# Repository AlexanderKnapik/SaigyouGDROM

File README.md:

SaigyouGDROM
========

SaigyouGDROM is a redesigned hardware implementation for Marcus Comstedt's
"iceGDROM". The aim of the project is to use the original software and gateware,
but with the hardware redesigned for a complete package.

This is currently a work in progress. Although the first revision prototypes have
been manufactured, there is still a lot to do in regards for testing and
recompiling the firmware and gateware for the new hardware.

For more information, please do visit the [original project](https://github.com/zeldin/iceGDROM).

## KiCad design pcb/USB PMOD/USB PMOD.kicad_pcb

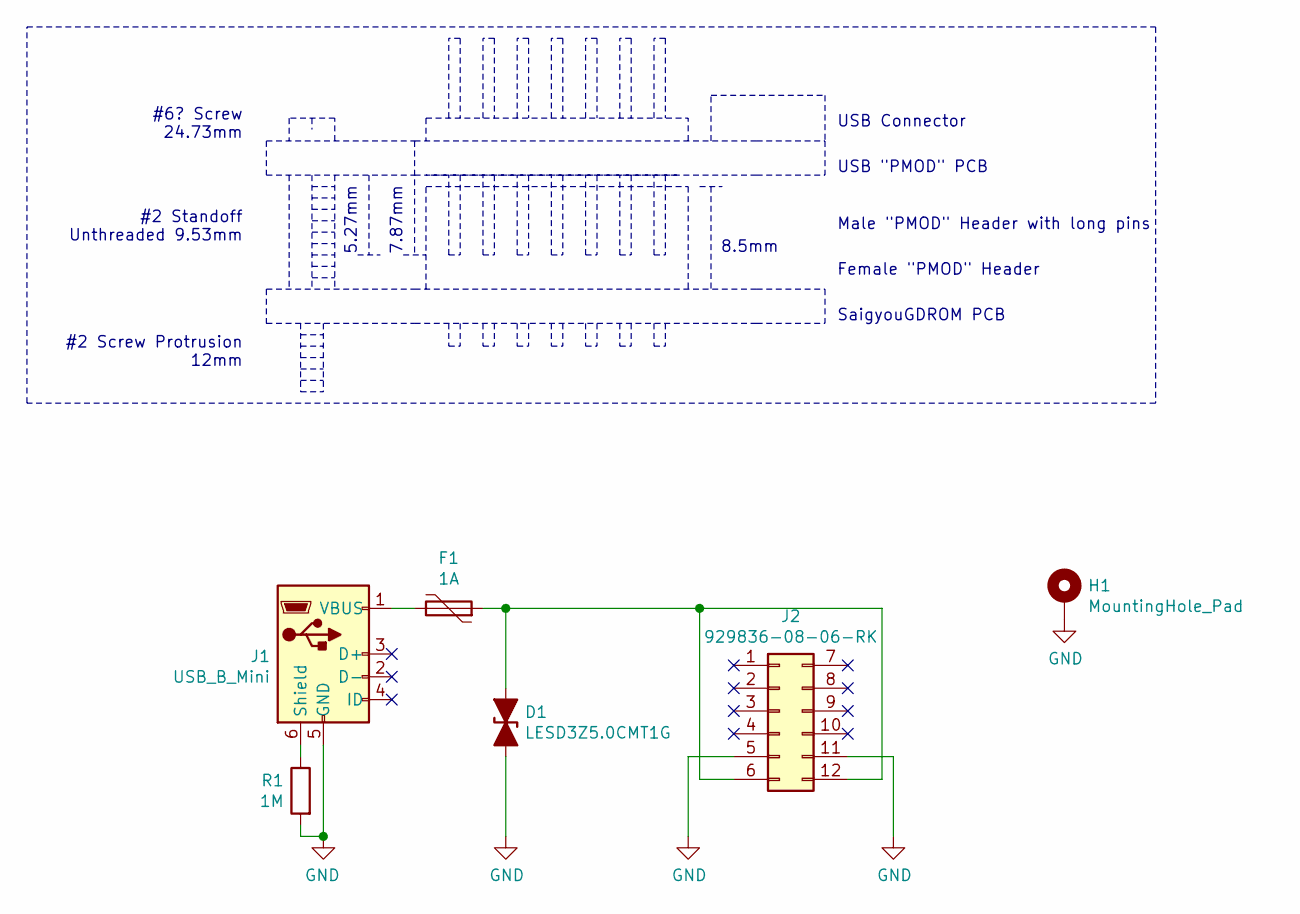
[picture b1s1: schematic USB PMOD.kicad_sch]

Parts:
D1: LESD3Z5.0CMT1G; D_SOD-323
F1: 1A; Fuse_1210_3225Metric_Castellated
H1: MountingHole_Pad; MountingHole_3.2mm_M3_Pad_Via
J1: USB_B_Mini; USB_Mini-B_Molex_657031020_Horizontal
J2: 929836-08-06-RK; PMOD_Host_2x06_P2.54mm_Vertical
R1: 1M; R_0603_1608Metric

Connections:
GND: D1.1 (A1), H1.1, J1.5 (GND), J2.5, J2.11, R1.2
unnamed: D1.2 (A2), F1.1, J2.6, J2.12
unnamed: F1.2, J1.1 (VBUS)
unnamed: J1.6 (Shield), R1.1

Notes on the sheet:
#6? Screw 24.73mm
#2 Standoff Unthreaded 9.53mm
#2 Screw Protrusion 12mm
5.27mm
7.87mm
8.5mm
USB Connector
USB "PMOD" PCB
Male "PMOD" Header with long pins
Female "PMOD" Header
SaigyouGDROM PCB

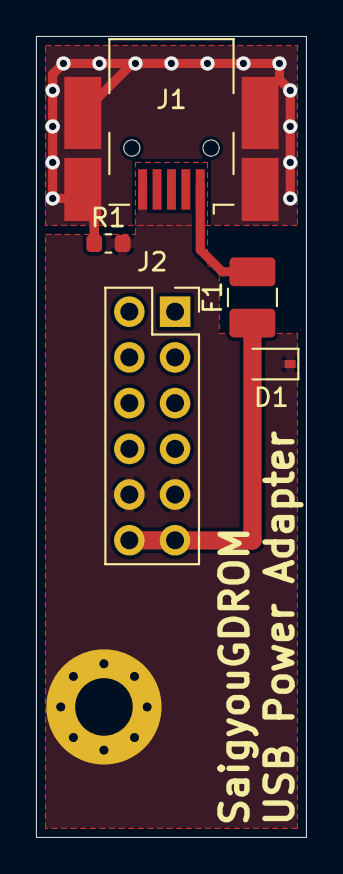
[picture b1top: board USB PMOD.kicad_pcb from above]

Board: 2 copper layers, 15.0 x 44.5 mm, 6 parts (0 on the bottom side), 4 nets.

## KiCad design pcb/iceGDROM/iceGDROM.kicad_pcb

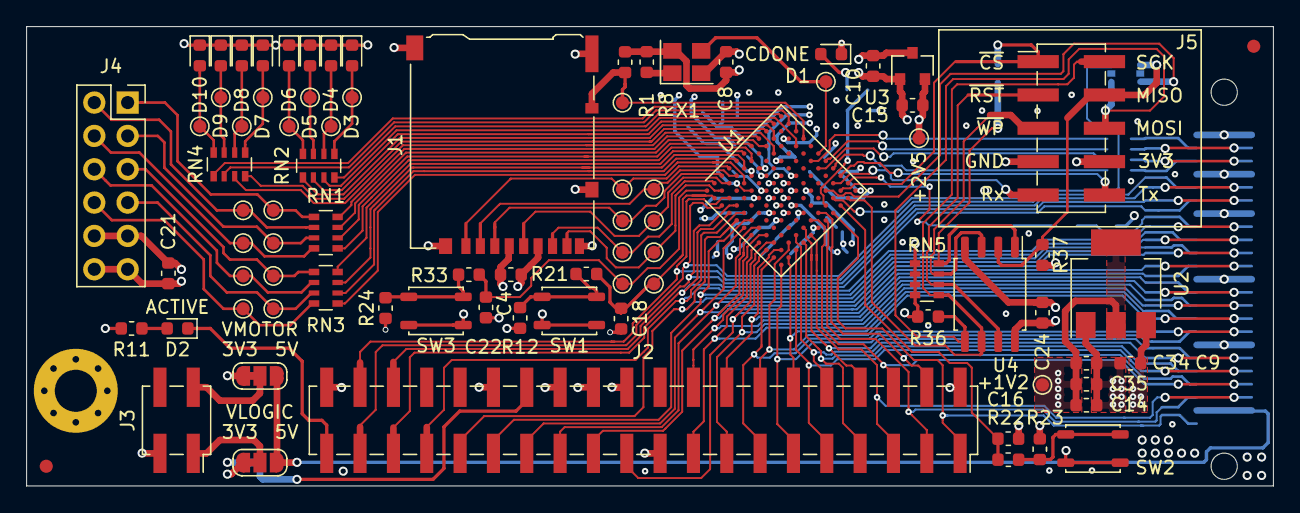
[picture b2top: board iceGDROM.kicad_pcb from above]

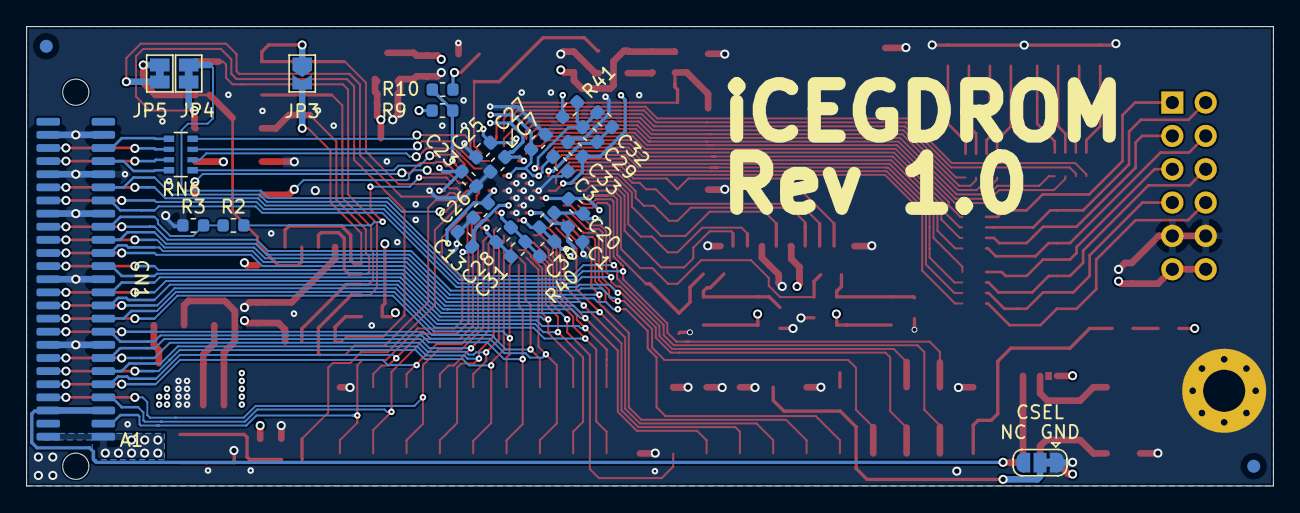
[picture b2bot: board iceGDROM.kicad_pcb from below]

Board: 4 copper layers, 95.0 x 35.0 mm, 114 parts (29 on the bottom side), 113 nets.

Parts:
+1V2, +2V5: TestPoint; TestPoint_Pad_D1.0mm
C1, C3, C4, C7, C8, C13, C20, C23, C24, C25, C26, C27, C28, C29, C30, C33: 100n; C_0603_1608Metric
C9, C14, C31, C32, C35: 10u; C_0603_1608Metric
C10, C15, C34: 1u0; C_0603_1608Metric
C16, C18, C22: 10n; C_0603_1608Metric
C21: NP; C_0603_1608Metric
CN1: Molex_52602_0579; Molex_052602_0579
D1, D2, D3, D4, D5, D6, D7, D8, D9, D10: LED; LED_0603_1608Metric
FID1, FID2, FID3, FID4: Fiducial; Fiducial_1mm_Mask2mm
H1: MountingHole_Pad; MountingHole_3.2mm_M3_Pad_Via
J1: Micro_SD_Card_Det_Hirose_DM3AT; microSD_HC_Hirose_DM3AT-SF-PEJM5
J2: Conn_02x20_Odd_Even; PinSocket_2x20_P2.54mm_Vertical_SMD
J3: Conn_02x02_Odd_Even; PinSocket_2x02_P2.54mm_Vertical_SMD
J4: PMOD; PMOD_Host_2x06_P2.54mm_Vertical
J5: Conn_02x05_Odd_Even; PinHeader_2x05_P2.54mm_Vertical_SMD
JP1: Jumper_NC_Dual; SolderJumper-3_P1.3mm_Bridged12_RoundedPad1.0x1.5mm
JP2, JP6: Jumper_3_Bridged12; SolderJumper-3_P1.3mm_Bridged12_RoundedPad1.0x1.5mm_NumberL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
JP3: SolderJumper_2_Bridged; SolderJumper-2_P1.3mm_Open_TrianglePad1.0x1.5mm
JP4, JP5: Jumper_NC_Small; SolderJumper-2_P1.3mm_Bridged_Pad1.0x1.5mm
R1, R3, R8, R12, R21, R22, R23, R24, R33: 10K; R_0603_1608Metric
R2, R40, R41: 100R; R_0603_1608Metric
R9: R; R_0603_1608Metric
R10, R11: 1K; R_0603_1608Metric
R36, R37: NP; R_0603_1608Metric
RN1, RN3, RN5: 10K; R_Array_Convex_4x0603
RN2, RN4: R_Pack04; R_Array_Convex_4x0603
RN6: 100R; R_Array_Convex_4x0603
SW1, SW2, SW3: SW_Push; SW_Push_SPST_NO_Alps_SKRP
TP2, TP3, TP4, TP5, TP6, TP7, TP8, TP9, TP10, TP11, TP12, TP13, TP14, TP15, TP16, TP17, TP18, TP36, TP37, TP38, TP39, TP41, TP42, TP43, TP44: TestPoint_Probe; TestPoint_Pad_D1.0mm
TP33: TestPoint; TestPoint_Pad_D1.0mm
U1: ICE40HX8K-BG121; BGA-121_9.0x9.0mm_Layout11x11_P0.8mm_Ball0.4mm_Pad0.35mm_NS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
U2: LD1117S12TR_SOT223; SOT-223-3_TabPin2
U3: ME6206A25M3G_SOT23; SOT-23
U4: W25Q32JVSS; SOIC-8_5.23x5.23mm_P1.27mm
X1: SG-310SCF; Crystal_SMD_3225-4Pin_3.2x2.5mm

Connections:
+1V2: +1V2.1, C14.1, C26.1, C27.1, C30.1, C33.1, C34.1, C35.1, R40.1, R41.1, U1.D4, U1.D8, U1.H4, U1.H8, U2.2
+2V5: +2V5.1, C15.1, C25.1, U1.C10, U3.2
+3V3: C1.2, C3.2, C4.1, C7.2, C8.1, C9.1, C10.1, C13.2, C20.2, C21.1, C23.1, C24.1, CN1.1, CN1.26, J1.4, J4.6, J4.12, J5.8, JP2.1, JP6.1, R1.1, R8.2, R9.2, R11.2, R23.2, R36.1, R37.1, RN5.5, RN5.6, RN5.7, RN5.8, SW1.1, SW3.1, U1.D6, U1.E4, U1.F8, U1.G4, U1.H6, U1.L11, U2.3, U3.3, U4.8, X1.4
+5V: CN1.3, CN1.28, JP2.3, JP6.3
+12V: CN1.25, CN1.50
/A0: CN1.19, J2.35, U1.D1
/A1: CN1.42, J2.33, U1.E2
/A2: CN1.44, J2.36, U1.D2
/ACTIVEn: D2.1, J2.39
/CD_CLK: CN1.48, RN6.2
/CS0n: CN1.20, J2.37, U1.C1
/CS1n: CN1.45, J2.38, U1.C2
/CSEL: J2.28, JP1.2
/D0: CN1.36, J2.17, U1.H1
/D1: CN1.11, J2.15, U1.J1
/D2: CN1.34, J2.13, U1.K1
/D3: CN1.9, J2.11, U1.L1
/D4: CN1.31, J2.9, U1.L3
/D5: CN1.6, J2.7, U1.L4
/D6: CN1.29, J2.5, U1.L5
/D7: CN1.4, J2.3, U1.L7
/D8: CN1.5, J2.4, U1.K7
/D9: CN1.30, J2.6, U1.K6
/D10: CN1.7, J2.8, U1.K5
/D11: CN1.32, J2.10, U1.K4
/D12: CN1.10, J2.12, U1.L2
/D13: CN1.35, J2.14, U1.K3
/D14: CN1.12, J2.16, U1.K2
/D15: CN1.37, J2.18, U1.H2
/DMACKn: CN1.16, J2.29, U1.F2
/DMARQ: CN1.14, J2.21, U1.J2
/EMPH: CN1.17, R2.1, R3.2
/FLASH_CSn: J5.1, JP3.1, U1.K10
/FLASH_MISO|IO1: J5.4, JP5.2, R37.2, U4.2
/FLASH_MOSI|IO0: J5.6, JP4.1, R36.2, U4.5
/FLASH_~RST~|IO3: J5.3, RN5.2, U4.7
/FLASH_~WP~|IO2: J5.5, RN5.3, U4.3
/FPGA_SCK: J5.2, RN5.1, U1.L10, U4.6
/FPGA_SDI: JP5.1, U1.J9
/FPGA_SDO: JP4.2, U1.K9
/G_RST: CN1.2, J2.1, U1.L8
/INTRQ: CN1.41, J2.31, U1.E1
/IO_RDY: CN1.40, J2.27, U1.F1
/LED0: RN2.4, U1.A11
/LED1: RN2.3, U1.D10
/LED2: RN2.2, U1.A10
/LED3: RN2.1, U1.B9
/LED4: RN4.4, U1.A9
/LED5: RN4.3, U1.C8
/LED6: RN4.2, U1.B11
/LED7: RN4.1, U1.C11
/LRCK: CN1.47, RN6.3
/PB0: R2.2, U1.K11
/PB1: J1.5, TP2.1, U1.B3
/PB2: J1.3, TP3.1, U1.A3
/PB3: J1.7, TP4.1, U1.A2
/PB4: J1.8, TP5.1, U1.B2
/PB5: J1.1, TP6.1, U1.A4
/PB6: J1.2, TP7.1, U1.B4
/PB7: J1.10, R1.2, TP8.1, U1.D11
/PMOD_1: RN1.8, U1.A8
/PMOD_2: RN1.6, U1.A7
/PMOD_3: RN3.8, U1.A6
/PMOD_4: RN3.6, U1.A5
/PMOD_5: RN1.7, U1.B8
/PMOD_6: RN1.5, U1.B6
/PMOD_7: RN3.7, U1.B5
/PMOD_8: RN3.5, U1.C4
/RDn: CN1.15, J2.25, U1.G2
/REFCLK: TP33.1, U1.F11, X1.3
/ROM_DWN: C18.1, R21.1, TP10.1, U1.B1
/ROM_UP: C22.1, R33.1, TP9.1, U1.A1
/SCK: CN1.22, RN6.4
/SDAT: CN1.23, RN6.1
/UART_Rx: J5.9, U1.J10
/UART_Tx: J5.10, U1.J11
/VLOGIC: J3.1, JP2.2
/VMOTOR: J3.2, JP6.2
/WRn: CN1.39, J2.23, U1.G1
GND: C1.1, C3.1, C4.2, C7.1, C8.2, C9.2, C10.2, C13.1, C14.2, C15.2, C16.1, C18.2, C20.1, C21.2, C22.2, C23.2, C24.2, C25.2, C26.2, C27.2, C30.2, C33.2, C34.2, C35.2, CN1.8, CN1.13, CN1.18, CN1.21, CN1.24, CN1.33, CN1.38, CN1.43, CN1.46, CN1.49, D1.1, D3.1, D4.1, D5.1, D6.1, D7.1, D8.1, D9.1, D10.1, H1.1, J1.6, J1.9, J1.11, J2.2, J2.19, J2.22, J2.24, J2.26, J2.30, J2.40, J3.3, J4.5, J4.11, J5.7, JP1.1, R3.1, R12.1, R24.1, SW2.2, U1.E5, U1.E6, U1.E7, U1.F5, U1.F6, U1.F7, U1.G5, U1.G6, U1.G7, U1.H5, U2.1, U3.1, U4.4, X1.2
unnamed: C16.2, R22.1, U1.L9
unnamed: C28.1, C31.1, R40.2, U1.J6
unnamed: C28.2, C31.2, U1.L6
unnamed: C29.1, C32.1, R41.2, U1.C6
unnamed: C29.2, C32.2, U1.C5
unnamed: D1.2, R10.2
unnamed: D2.2, R11.1
unnamed: D3.2, RN2.5, TP11.1
unnamed: D4.2, RN2.6, TP12.1
unnamed: D5.2, RN2.7, TP13.1
unnamed: D6.2, RN2.8, TP14.1
unnamed: D7.2, RN4.5, TP15.1
unnamed: D8.2, RN4.6, TP16.1
unnamed: D9.2, RN4.7, TP17.1
unnamed: D10.2, RN4.8, TP18.1
unnamed: J4.1, RN1.1, TP36.1
unnamed: J4.2, RN1.3, TP37.1
unnamed: J4.3, RN3.1, TP38.1
unnamed: J4.4, RN3.3, TP39.1
unnamed: J4.7, RN1.2, TP41.1
unnamed: J4.8, RN1.4, TP42.1
unnamed: J4.9, RN3.2, TP43.1
unnamed: J4.10, RN3.4, TP44.1
unnamed: JP3.2, RN5.4, U4.1
unnamed: R8.1, X1.1
unnamed: R9.1, R10.1, U1.K8
unnamed: R12.2, R21.2, SW1.2
unnamed: R22.2, R23.1, SW2.1
unnamed: R24.2, R33.2, SW3.2
unnamed: RN6.5, U1.H11
unnamed: RN6.6, U1.G10
unnamed: RN6.7, U1.G11
unnamed: RN6.8, U1.F10

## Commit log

2019-07-18 Adding work so far on an integrated PCB schematic.
2019-07-24 Included the SPI Memory card into the schematic as a major point. Created a footprint for the tactile button being used and including the 3D model due to no NC clause.
2019-07-27 Finishing up the peripherals for the FPGA in the schematic, adding the CRESET and CDONE circuits and decoupling for IO power pins.
2019-07-28 Completed a functional version of the schematic and started with basic layout of the components on the PCB.
2019-07-28 Fixing the Molex header pin position and adding a 3D model path to it.
2019-07-28 Split the IDE header into 40+4 due to SMD header availability. Started with layout of the PCB.
2019-08-23 Completed functionality of the PCB layout. Still have to do the silkscreen though.
2019-11-24 Finalising the silkscreen & the schematic page
2021-04-27 Adding latest hardware changes and including USB PMOD project for powering the unit for testing.
2021-04-27 Adding pictures and new readme file.
2021-04-27 Fixing mistakes in readme.
2021-04-27 Deleting backup files from git repository, and updating the USB PMOD board to latest nightly build.
2021-04-27 Fixing name of image in readme.
